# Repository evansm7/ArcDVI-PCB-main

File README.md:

# ArcDVI main board

Kicad 6.0 PCB design for the ArcDVI main board:

This board interfaces via FFC to an ArcDVI VIDC board (either the socket-based interposer for A4xx machines, or the push-on for A3000/A5000).

See <https://stardot.org.uk> for more info.

# License

ArcDVI is copyright 2023 Matt Evans.

This work is licensed under the Creative Commons Attribution-NonCommercial-ShareAlike 3.0 Unported License. To view a copy of this license, visit http://creativecommons.org/licenses/by-nc-sa/3.0/ or send a letter to Creative Commons, PO Box 1866, Mountain View, CA 94042, USA.

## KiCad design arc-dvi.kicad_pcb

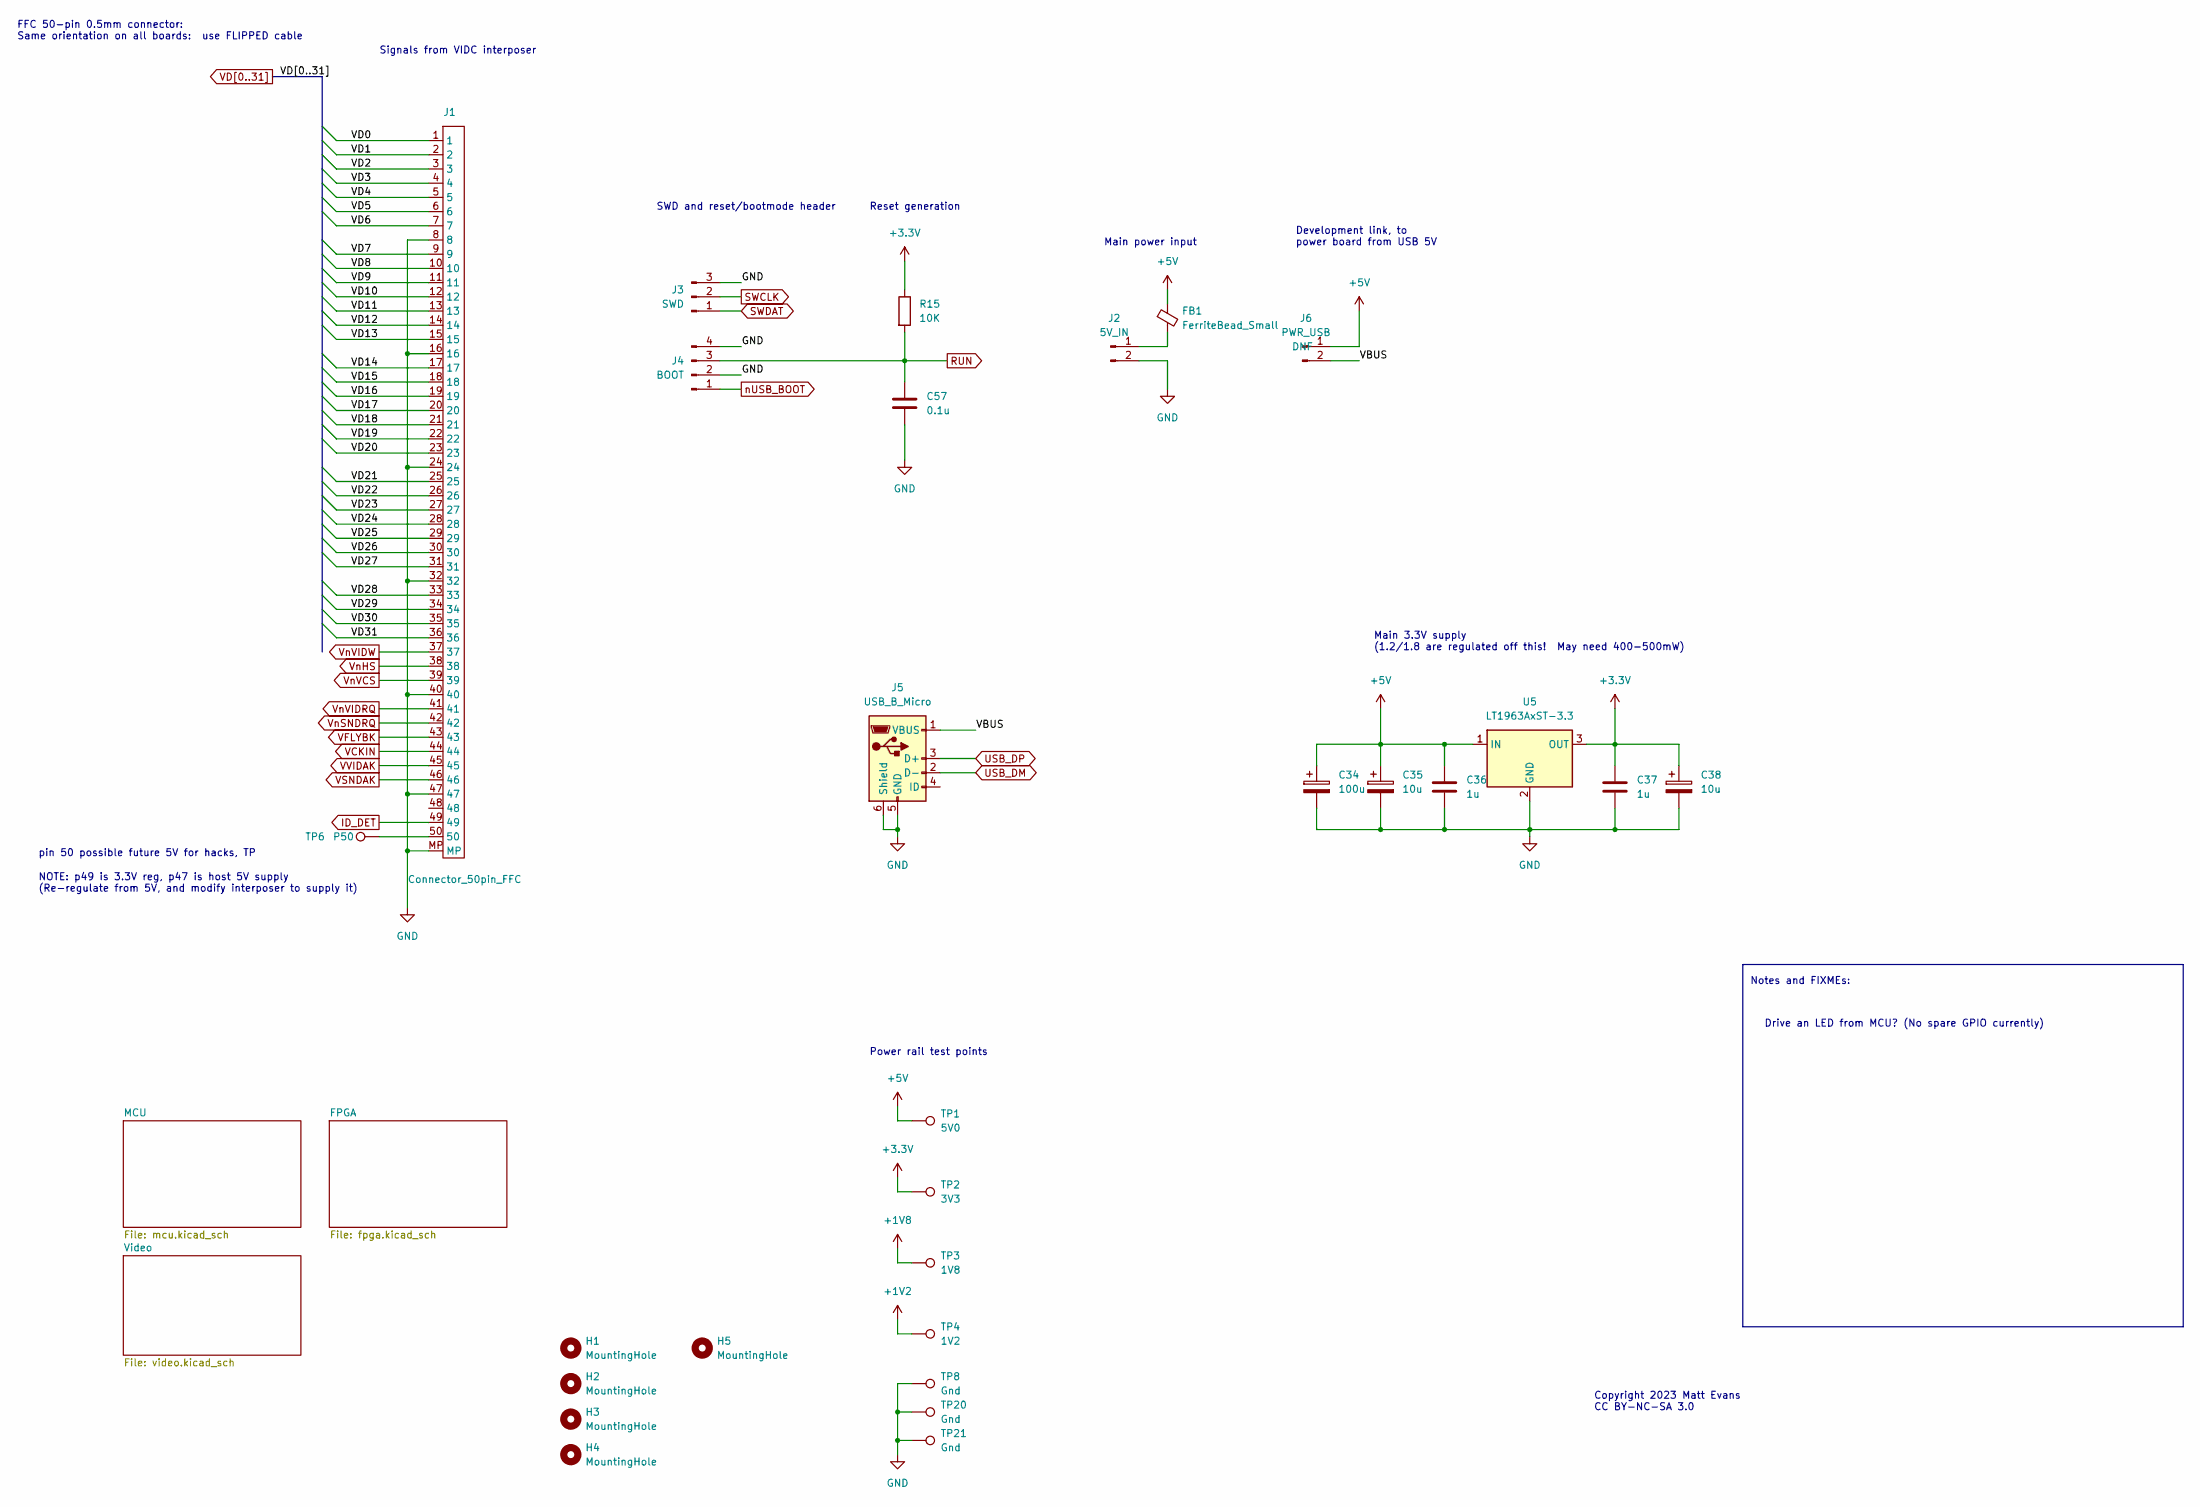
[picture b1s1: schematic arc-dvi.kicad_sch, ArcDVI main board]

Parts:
C34: 100u; CP_EIA-3528-21_Kemet-B
C35, C38: 10u; CP_EIA-3528-21_Kemet-B
C36, C37: 1u; C_0603_1608Metric
C57: 0.1u; C_0603_1608Metric
FB1: FerriteBead_Small; L_0805_2012Metric
H1, H2, H3, H4, H5: MountingHole; MountingHole_3.2mm_M3
J1: Connector_50pin_FFC; Hirose_FH12-50S-0.5SH_1x50-1MP_P0.50mm_Horizontal
J2: 5V_IN; PinHeader_1x02_P2.54mm_Horizontal
J3: SWD; PinHeader_1x03_P2.54mm_Vertical
J4: BOOT; PinHeader_1x04_P2.54mm_Vertical
J5: USB_B_Micro; USB_Micro-B_Amphenol_10104110_Horizontal
J6: PWR_USB; PinHeader_1x02_P2.54mm_Vertical
R15: 10K; R_0603_1608Metric
TP1: 5V0; TestPoint_Pad_1.5x1.5mm
TP2: 3V3; TestPoint_Pad_1.5x1.5mm
TP3: 1V8; TestPoint_Pad_1.5x1.5mm
TP4: 1V2; TestPoint_Pad_1.5x1.5mm
TP6: P50; TestPoint_Pad_D1.0mm
TP8, TP20, TP21: Gnd; TestPoint_Pad_1.5x1.5mm
U5: LT1963AxST-3.3; SOT-223-3_TabPin2

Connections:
+1V2: TP4.1; also elsewhere on the board
+1V8: TP3.1; also elsewhere on the board
+3V3: C37.1, C38.1, R15.1, TP2.1, U5.3 (OUT); also elsewhere on the board
+5V: C34.1, C35.1, C36.1, FB1.1, J6.1, TP1.1, U5.1 (IN); also elsewhere on the board
/VBUS: J5.1 (VBUS), J6.2
GND: C34.2, C35.2, C36.2, C37.2, C38.2, C57.2, J1.8, J1.16, J1.24, J1.32, J1.40, J1.47, J1.MP, J2.2, J3.3, J4.2, J4.4, J5.5 (GND), J5.6 (Shield), TP8.1, TP20.1, TP21.1, U5.2 (GND); also elsewhere on the board
ID_DET: J1.49; also elsewhere on the board
unnamed: FB1.2, J2.1
unnamed: J1.50, TP6.1
RUN: C57.1, J4.3, R15.2; also elsewhere on the board
SWCLK: J3.2; also elsewhere on the board
SWDAT: J3.1; also elsewhere on the board
USB_DM: J5.2 (D-); also elsewhere on the board
USB_DP: J5.3 (D+); also elsewhere on the board
VCKIN: J1.44; also elsewhere on the board
VD0: J1.1; also elsewhere on the board
VD1: J1.2; also elsewhere on the board
VD2: J1.3; also elsewhere on the board
VD3: J1.4; also elsewhere on the board
VD4: J1.5; also elsewhere on the board
VD5: J1.6; also elsewhere on the board
VD6: J1.7; also elsewhere on the board
VD7: J1.9; also elsewhere on the board
VD8: J1.10; also elsewhere on the board
VD9: J1.11; also elsewhere on the board
VD10: J1.12; also elsewhere on the board
VD11: J1.13; also elsewhere on the board
VD12: J1.14; also elsewhere on the board
VD13: J1.15; also elsewhere on the board
VD14: J1.17; also elsewhere on the board
VD15: J1.18; also elsewhere on the board
VD16: J1.19; also elsewhere on the board
VD17: J1.20; also elsewhere on the board
VD18: J1.21; also elsewhere on the board
VD19: J1.22; also elsewhere on the board
VD20: J1.23; also elsewhere on the board
VD21: J1.25; also elsewhere on the board
VD22: J1.26; also elsewhere on the board
VD23: J1.27; also elsewhere on the board
VD24: J1.28; also elsewhere on the board
VD25: J1.29; also elsewhere on the board
VD26: J1.30; also elsewhere on the board
VD27: J1.31; also elsewhere on the board
VD28: J1.33; also elsewhere on the board
VD29: J1.34; also elsewhere on the board
VD30: J1.35; also elsewhere on the board
VD31: J1.36; also elsewhere on the board
VFLYBK: J1.43; also elsewhere on the board
VSNDAK: J1.46; also elsewhere on the board
VVIDAK: J1.45; also elsewhere on the board
VnHS: J1.38; also elsewhere on the board
VnSNDRQ: J1.42; also elsewhere on the board
VnVCS: J1.39; also elsewhere on the board
VnVIDRQ: J1.41; also elsewhere on the board
VnVIDW: J1.37; also elsewhere on the board
nUSB_BOOT: J4.1; also elsewhere on the board

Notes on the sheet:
Reset generation
Notes and FIXMEs:
Power rail test points
Copyright 2023 Matt Evans CC BY-NC-SA 3.0
Development link, to power board from USB 5V
NOTE: p49 is 3.3V reg, p47 is host 5V supply (Re-regulate from 5V, and modify interposer to supply it)
Main 3.3V supply (1.2/1.8 are regulated off this! May need 400-500mW)
Signals from VIDC interposer
SWD and reset/bootmode header
pin 50 possible future 5V for hacks, TP
Drive an LED from MCU? (No spare GPIO currently)
FFC 50-pin 0.5mm connector: Same orientation on all boards: use FLIPPED cable
Main power input

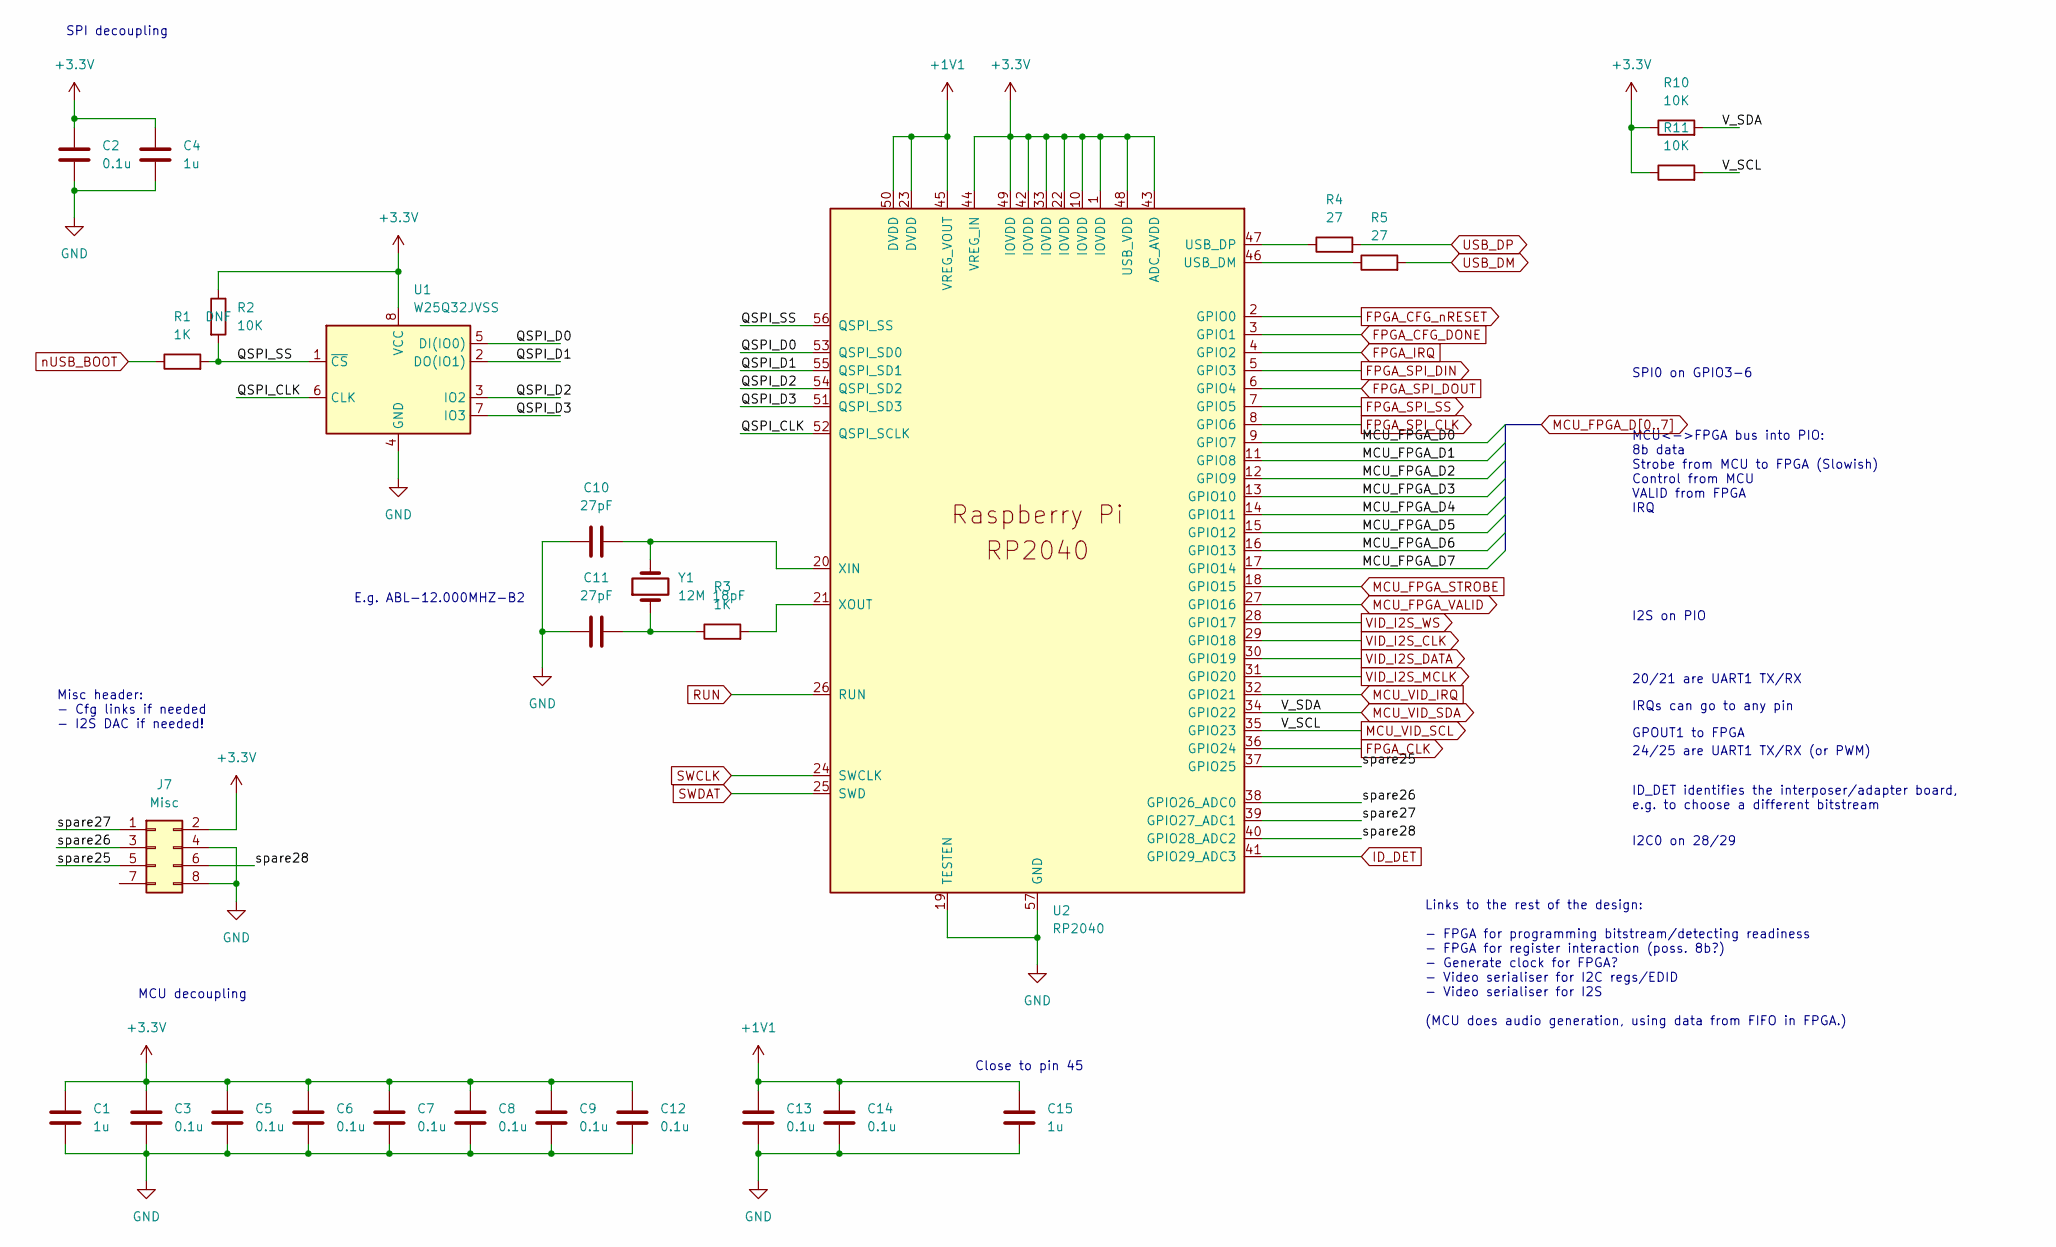
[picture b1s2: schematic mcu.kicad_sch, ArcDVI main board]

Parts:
C1, C4, C15: 1u; C_0603_1608Metric
C2, C3, C5, C6, C7, C8, C9, C12, C13, C14: 0.1u; C_0603_1608Metric
C10, C11: 27pF; C_0603_1608Metric
J7: Misc; PinHeader_2x04_P2.54mm_Vertical
R1, R3: 1K; R_0603_1608Metric
R2, R10, R11: 10K; R_0603_1608Metric
R4, R5: 27; R_0603_1608Metric
U1: W25Q32JVSS; SOIC-8_5.23x5.23mm_P1.27mm
U2: RP2040; RP2040-QFN-56
Y1: 12M 18pF; Crystal_SMD_ABLS7M

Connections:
+1V1: C13.1, C14.1, C15.1, U2.23 (DVDD), U2.45 (VREG_VOUT), U2.50 (DVDD)
+3V3: C1.1, C2.1, C3.1, C4.1, C5.1, C6.1, C7.1, C8.1, C9.1, C12.1, J7.2, R2.1, R10.1, R11.1, U1.8 (VCC), U2.1 (IOVDD), U2.10 (IOVDD), U2.22 (IOVDD), U2.33 (IOVDD), U2.42 (IOVDD), U2.43 (ADC_AVDD), U2.44 (VREG_IN), U2.48 (USB_VDD), U2.49 (IOVDD); also elsewhere on the board
/MCU/QSPI_CLK: U1.6 (CLK), U2.52 (QSPI_SCLK)
/MCU/QSPI_D0: U1.5 (DI(IO0)), U2.53 (QSPI_SD0)
/MCU/QSPI_D1: U1.2 (DO(IO1)), U2.55 (QSPI_SD1)
/MCU/QSPI_D2: U1.3 (IO2), U2.54 (QSPI_SD2)
/MCU/QSPI_D3: U1.7 (IO3), U2.51 (QSPI_SD3)
/MCU/QSPI_SS: R1.2, R2.2, U1.1 (~CS), U2.56 (QSPI_SS)
/MCU/spare25: J7.5, U2.37 (GPIO25)
/MCU/spare26: J7.3, U2.38 (GPIO26_ADC0)
/MCU/spare27: J7.1, U2.39 (GPIO27_ADC1)
/MCU/spare28: J7.6, U2.40 (GPIO28_ADC2)
FPGA_CFG_DONE: U2.3 (GPIO1); also elsewhere on the board
FPGA_CFG_nRESET: U2.2 (GPIO0); also elsewhere on the board
FPGA_CLK: U2.36 (GPIO24); also elsewhere on the board
FPGA_IRQ: U2.4 (GPIO2); also elsewhere on the board
FPGA_SPI_CLK: U2.8 (GPIO6); also elsewhere on the board
FPGA_SPI_DIN: U2.5 (GPIO3); also elsewhere on the board
FPGA_SPI_DOUT: U2.6 (GPIO4); also elsewhere on the board
FPGA_SPI_SS: U2.7 (GPIO5); also elsewhere on the board
GND: C1.2, C2.2, C3.2, C4.2, C5.2, C6.2, C7.2, C8.2, C9.2, C10.1, C11.1, C12.2, C13.2, C14.2, C15.2, J7.4, J7.8, U1.4 (GND), U2.19 (TESTEN), U2.57 (GND); also elsewhere on the board
ID_DET: U2.41 (GPIO29_ADC3); also elsewhere on the board
MCU_FPGA_D0: U2.9 (GPIO7); also elsewhere on the board
MCU_FPGA_D1: U2.11 (GPIO8); also elsewhere on the board
MCU_FPGA_D2: U2.12 (GPIO9); also elsewhere on the board
MCU_FPGA_D3: U2.13 (GPIO10); also elsewhere on the board
MCU_FPGA_D4: U2.14 (GPIO11); also elsewhere on the board
MCU_FPGA_D5: U2.15 (GPIO12); also elsewhere on the board
MCU_FPGA_D6: U2.16 (GPIO13); also elsewhere on the board
MCU_FPGA_D7: U2.17 (GPIO14); also elsewhere on the board
MCU_FPGA_STROBE: U2.18 (GPIO15); also elsewhere on the board
MCU_FPGA_VALID: U2.27 (GPIO16); also elsewhere on the board
MCU_VID_IRQ: U2.32 (GPIO21); also elsewhere on the board
MCU_VID_SCL: R11.2, U2.35 (GPIO23); also elsewhere on the board
MCU_VID_SDA: R10.2, U2.34 (GPIO22); also elsewhere on the board
unnamed: C10.2, U2.20 (XIN), Y1.2
unnamed: C11.2, R3.1, Y1.1
unnamed: R3.2, U2.21 (XOUT)
unnamed: R4.1, U2.47 (USB_DP)
unnamed: R5.1, U2.46 (USB_DM)
RUN: U2.26 (RUN); also elsewhere on the board
SWCLK: U2.24 (SWCLK); also elsewhere on the board
SWDAT: U2.25 (SWD); also elsewhere on the board
USB_DM: R5.2; also elsewhere on the board
USB_DP: R4.2; also elsewhere on the board
VID_I2S_CLK: U2.29 (GPIO18); also elsewhere on the board
VID_I2S_DATA: U2.30 (GPIO19); also elsewhere on the board
VID_I2S_MCLK: U2.31 (GPIO20); also elsewhere on the board
VID_I2S_WS: U2.28 (GPIO17); also elsewhere on the board
nUSB_BOOT: R1.1; also elsewhere on the board

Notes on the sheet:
MCU decoupling
20/21 are UART1 TX/RX
Misc header: - Cfg links if needed - I2S DAC if needed!
Links to the rest of the design: - FPGA for programming bitstream/detecting readiness - FPGA for register interaction (poss. 8b?) - Generate clock for FPGA? - Video serialiser for I2C regs/EDID - Video serialiser for I2S (MCU does audio generation, using data from FIFO in FPGA.)
IRQs can go to any pin
E.g. ABL-12.000MHZ-B2
I2S on PIO
GPOUT1 to FPGA
SPI decoupling
24/25 are UART1 TX/RX (or PWM)
I2C0 on 28/29
Close to pin 45
MCU<->FPGA bus into PIO: 8b data Strobe from MCU to FPGA (Slowish) Control from MCU VALID from FPGA IRQ
SPI0 on GPIO3-6
ID_DET identifies the interposer/adapter board, e.g. to choose a different bitstream

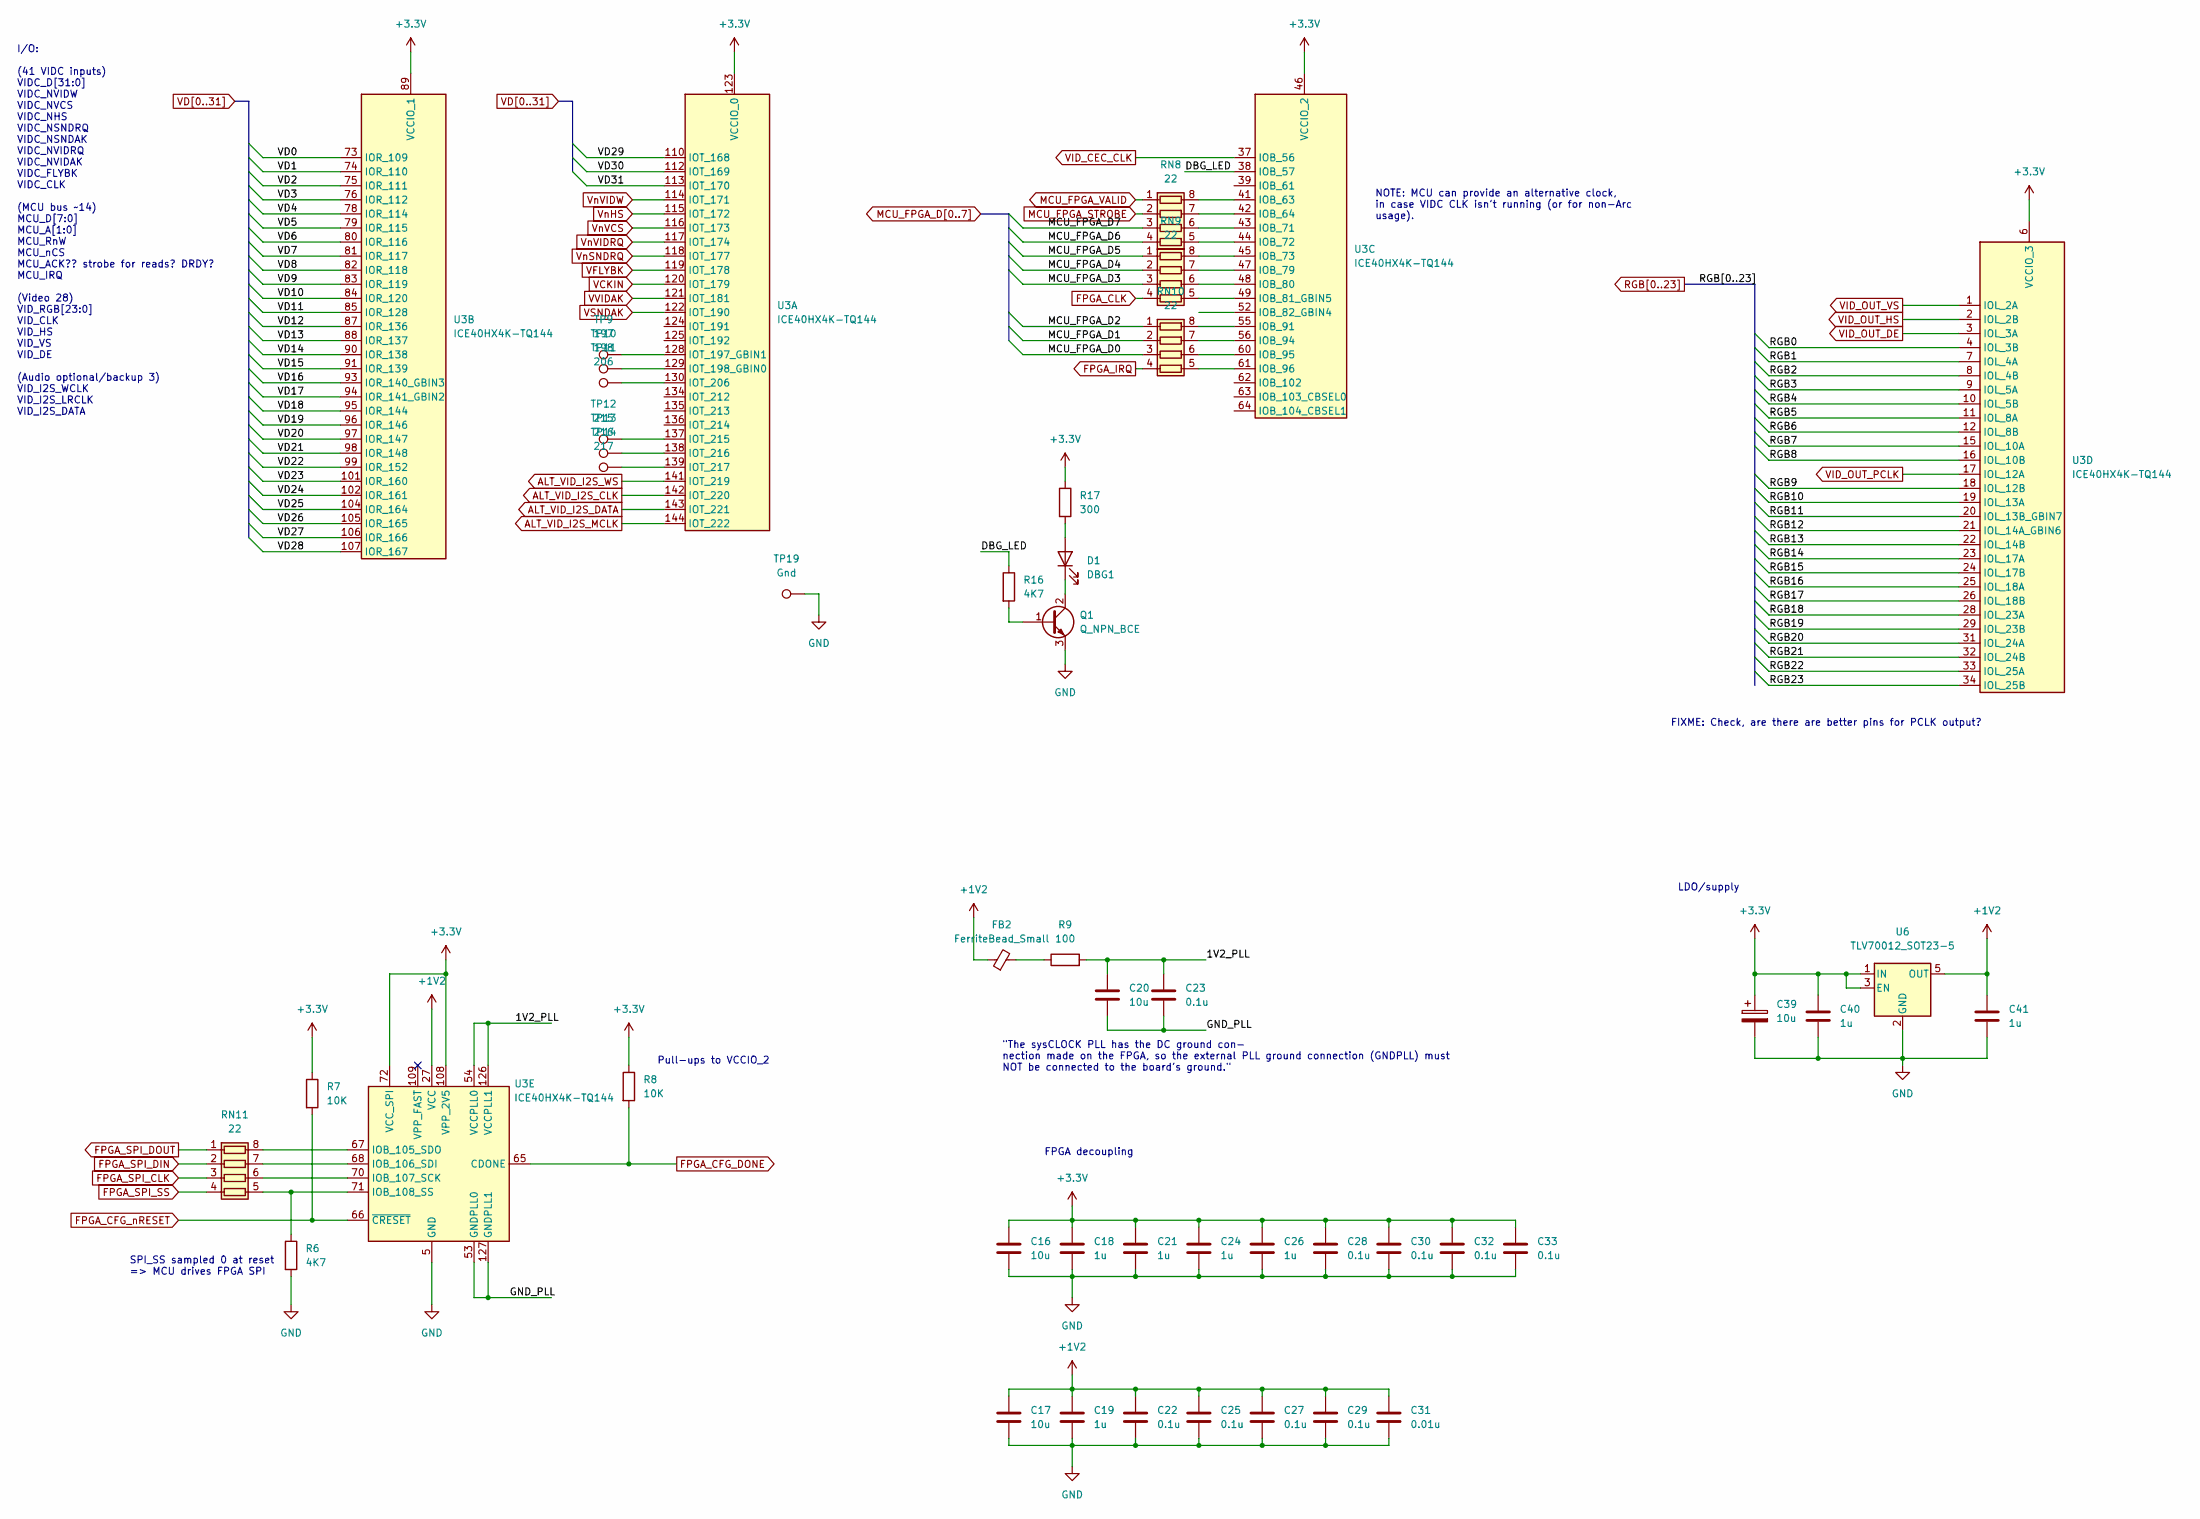
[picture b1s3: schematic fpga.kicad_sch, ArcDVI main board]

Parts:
C16, C17, C20: 10u; C_0805_2012Metric
C18, C19, C21, C24, C26, C40, C41: 1u; C_0603_1608Metric
C22, C23, C25, C27, C28, C29, C30, C32, C33: 0.1u; C_0603_1608Metric
C31: 0.01u; C_0603_1608Metric
C39: 10u; CP_EIA-3528-21_Kemet-B
D1: DBG1; LED_0805_2012Metric
FB2: FerriteBead_Small; L_0603_1608Metric
Q1: Q_NPN_BCE; SOT-23
R6, R16: 4K7; R_0603_1608Metric
R7, R8: 10K; R_0603_1608Metric
R9: 100; R_0603_1608Metric
R17: 300; R_0603_1608Metric
RN8, RN9, RN10, RN11: 22; R_Array_Convex_4x0603
TP9: 197; TestPoint_Pad_D1.0mm
TP10: 198; TestPoint_Pad_D1.0mm
TP11: 206; TestPoint_Pad_D1.0mm
TP12: 215; TestPoint_Pad_D1.0mm
TP13: 216; TestPoint_Pad_D1.0mm
TP14: 217; TestPoint_Pad_D1.0mm
TP19: Gnd; TestPoint_Pad_1.5x1.5mm
U3: ICE40HX4K-TQ144; TQFP-144_20x20mm_P0.5mm
U6: TLV70012_SOT23-5; SOT-23-5

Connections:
+1V2: C17.1, C19.1, C22.1, C25.1, C27.1, C29.1, C31.1, C41.1, FB2.1, U3.27 (VCC), U3.40 (VCC), U3.92 (VCC), U3.111 (VCC), U6.5 (OUT); also elsewhere on the board
+3V3: C16.1, C18.1, C21.1, C24.1, C26.1, C28.1, C30.1, C32.1, C33.1, C39.1, C40.1, R7.1, R8.1, R17.1, U3.6 (VCCIO_3), U3.30 (VCCIO_3), U3.46 (VCCIO_2), U3.57 (VCCIO_2), U3.72 (VCC_SPI), U3.89 (VCCIO_1), U3.100 (VCCIO_1), U3.108 (VPP_2V5), U3.123 (VCCIO_0), U3.131 (VCCIO_0), U6.1 (IN), U6.3 (EN); also elsewhere on the board
/FPGA/1V2_PLL: C20.1, C23.1, R9.2, U3.54 (VCCPLL0), U3.126 (VCCPLL1)
/FPGA/DBG_LED: R16.1, U3.38 (IOB_57)
/FPGA/GND_PLL: C20.2, C23.2, U3.53 (GNDPLL0), U3.127 (GNDPLL1)
ALT_VID_I2S_CLK: U3.142 (IOT_220); also elsewhere on the board
ALT_VID_I2S_DATA: U3.143 (IOT_221); also elsewhere on the board
ALT_VID_I2S_MCLK: U3.144 (IOT_222); also elsewhere on the board
ALT_VID_I2S_WS: U3.141 (IOT_219); also elsewhere on the board
FPGA_CFG_DONE: R8.2, U3.65 (CDONE); also elsewhere on the board
FPGA_CFG_nRESET: R7.2, U3.66 (~CRESET); also elsewhere on the board
FPGA_CLK: RN9.4 (R4.1); also elsewhere on the board
FPGA_IRQ: RN10.4 (R4.1); also elsewhere on the board
FPGA_SPI_CLK: RN11.3 (R3.1); also elsewhere on the board
FPGA_SPI_DIN: RN11.2 (R2.1); also elsewhere on the board
FPGA_SPI_DOUT: RN11.1 (R1.1); also elsewhere on the board
FPGA_SPI_SS: RN11.4 (R4.1); also elsewhere on the board
GND: C16.2, C17.2, C18.2, C19.2, C21.2, C22.2, C24.2, C25.2, C26.2, C27.2, C28.2, C29.2, C30.2, C31.2, C32.2, C33.2, C39.2, C40.2, C41.2, Q1.3 (E), R6.2, TP19.1, U3.5 (GND), U3.13 (GND), U3.14 (GND), U3.59 (GND), U3.69 (GND), U3.86 (GND), U3.103 (GND), U3.132 (GND), U3.140 (GND), U6.2 (GND); also elsewhere on the board
MCU_FPGA_D0: RN10.3 (R3.1); also elsewhere on the board
MCU_FPGA_D1: RN10.2 (R2.1); also elsewhere on the board
MCU_FPGA_D2: RN10.1 (R1.1); also elsewhere on the board
MCU_FPGA_D3: RN9.3 (R3.1); also elsewhere on the board
MCU_FPGA_D4: RN9.2 (R2.1); also elsewhere on the board
MCU_FPGA_D5: RN9.1 (R1.1); also elsewhere on the board
MCU_FPGA_D6: RN8.4 (R4.1); also elsewhere on the board
MCU_FPGA_D7: RN8.3 (R3.1); also elsewhere on the board
MCU_FPGA_STROBE: RN8.2 (R2.1); also elsewhere on the board
MCU_FPGA_VALID: RN8.1 (R1.1); also elsewhere on the board
unnamed: D1.1 (K), Q1.2 (C)
unnamed: D1.2 (A), R17.2
unnamed: FB2.2, R9.1
unnamed: Q1.1 (B), R16.2
unnamed: R6.1, RN11.5 (R4.2), U3.71 (IOB_108_SS)
unnamed: RN8.5 (R4.2), U3.44 (IOB_72)
unnamed: RN8.6 (R3.2), U3.43 (IOB_71)
unnamed: RN8.7 (R2.2), U3.42 (IOB_64)
unnamed: RN8.8 (R1.2), U3.41 (IOB_63)
unnamed: RN9.5 (R4.2), U3.49 (IOB_81_GBIN5)
unnamed: RN9.6 (R3.2), U3.48 (IOB_80)
unnamed: RN9.7 (R2.2), U3.47 (IOB_79)
unnamed: RN9.8 (R1.2), U3.45 (IOB_73)
unnamed: RN10.5 (R4.2), U3.61 (IOB_96)
unnamed: RN10.6 (R3.2), U3.60 (IOB_95)
unnamed: RN10.7 (R2.2), U3.56 (IOB_94)
unnamed: RN10.8 (R1.2), U3.55 (IOB_91)
unnamed: RN11.6 (R3.2), U3.70 (IOB_107_SCK)
unnamed: RN11.7 (R2.2), U3.68 (IOB_106_SDI)
unnamed: RN11.8 (R1.2), U3.67 (IOB_105_SDO)
unnamed: TP9.1, U3.128 (IOT_197_GBIN1)
unnamed: TP10.1, U3.129 (IOT_198_GBIN0)
unnamed: TP11.1, U3.130 (IOT_206)
unnamed: TP12.1, U3.137 (IOT_215)
unnamed: TP13.1, U3.138 (IOT_216)
unnamed: TP14.1, U3.139 (IOT_217)
RGB0: U3.4 (IOL_3B); also elsewhere on the board
RGB1: U3.7 (IOL_4A); also elsewhere on the board
RGB2: U3.8 (IOL_4B); also elsewhere on the board
RGB3: U3.9 (IOL_5A); also elsewhere on the board
RGB4: U3.10 (IOL_5B); also elsewhere on the board
RGB5: U3.11 (IOL_8A); also elsewhere on the board
RGB6: U3.12 (IOL_8B); also elsewhere on the board
RGB7: U3.15 (IOL_10A); also elsewhere on the board
RGB8: U3.16 (IOL_10B); also elsewhere on the board
RGB9: U3.18 (IOL_12B); also elsewhere on the board
RGB10: U3.19 (IOL_13A); also elsewhere on the board
RGB11: U3.20 (IOL_13B_GBIN7); also elsewhere on the board
RGB12: U3.21 (IOL_14A_GBIN6); also elsewhere on the board
RGB13: U3.22 (IOL_14B); also elsewhere on the board
RGB14: U3.23 (IOL_17A); also elsewhere on the board
RGB15: U3.24 (IOL_17B); also elsewhere on the board
RGB16: U3.25 (IOL_18A); also elsewhere on the board
RGB17: U3.26 (IOL_18B); also elsewhere on the board
RGB18: U3.28 (IOL_23A); also elsewhere on the board
RGB19: U3.29 (IOL_23B); also elsewhere on the board
RGB20: U3.31 (IOL_24A); also elsewhere on the board
RGB21: U3.32 (IOL_24B); also elsewhere on the board
RGB22: U3.33 (IOL_25A); also elsewhere on the board
RGB23: U3.34 (IOL_25B); also elsewhere on the board
VCKIN: U3.120 (IOT_179); also elsewhere on the board
VD0: U3.73 (IOR_109); also elsewhere on the board
VD1: U3.74 (IOR_110); also elsewhere on the board
VD2: U3.75 (IOR_111); also elsewhere on the board
VD3: U3.76 (IOR_112); also elsewhere on the board
VD4: U3.78 (IOR_114); also elsewhere on the board
VD5: U3.79 (IOR_115); also elsewhere on the board
VD6: U3.80 (IOR_116); also elsewhere on the board
VD7: U3.81 (IOR_117); also elsewhere on the board
VD8: U3.82 (IOR_118); also elsewhere on the board
VD9: U3.83 (IOR_119); also elsewhere on the board
VD10: U3.84 (IOR_120); also elsewhere on the board
VD11: U3.85 (IOR_128); also elsewhere on the board
VD12: U3.87 (IOR_136); also elsewhere on the board
VD13: U3.88 (IOR_137); also elsewhere on the board
VD14: U3.90 (IOR_138); also elsewhere on the board
VD15: U3.91 (IOR_139); also elsewhere on the board
VD16: U3.93 (IOR_140_GBIN3); also elsewhere on the board
VD17: U3.94 (IOR_141_GBIN2); also elsewhere on the board
VD18: U3.95 (IOR_144); also elsewhere on the board
VD19: U3.96 (IOR_146); also elsewhere on the board
VD20: U3.97 (IOR_147); also elsewhere on the board
VD21: U3.98 (IOR_148); also elsewhere on the board
VD22: U3.99 (IOR_152); also elsewhere on the board
VD23: U3.101 (IOR_160); also elsewhere on the board
VD24: U3.102 (IOR_161); also elsewhere on the board
VD25: U3.104 (IOR_164); also elsewhere on the board
VD26: U3.105 (IOR_165); also elsewhere on the board
VD27: U3.106 (IOR_166); also elsewhere on the board
VD28: U3.107 (IOR_167); also elsewhere on the board
VD29: U3.110 (IOT_168); also elsewhere on the board
VD30: U3.112 (IOT_169); also elsewhere on the board
VD31: U3.113 (IOT_170); also elsewhere on the board
VFLYBK: U3.119 (IOT_178); also elsewhere on the board
VID_CEC_CLK: U3.37 (IOB_56); also elsewhere on the board
VID_OUT_DE: U3.3 (IOL_3A); also elsewhere on the board
VID_OUT_HS: U3.2 (IOL_2B); also elsewhere on the board
VID_OUT_PCLK: U3.17 (IOL_12A); also elsewhere on the board
VID_OUT_VS: U3.1 (IOL_2A); also elsewhere on the board
VSNDAK: U3.122 (IOT_190); also elsewhere on the board
VVIDAK: U3.121 (IOT_181); also elsewhere on the board
VnHS: U3.115 (IOT_172); also elsewhere on the board
VnSNDRQ: U3.118 (IOT_177); also elsewhere on the board
VnVCS: U3.116 (IOT_173); also elsewhere on the board
VnVIDRQ: U3.117 (IOT_174); also elsewhere on the board
VnVIDW: U3.114 (IOT_171); also elsewhere on the board

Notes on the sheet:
Pull-ups to VCCIO_2
SPI_SS sampled 0 at reset => MCU drives FPGA SPI
FIXME: Check, are there are better pins for PCLK output?
LDO/supply
"The sysCLOCK PLL has the DC ground con- nection made on the FPGA, so the external PLL ground connection (GNDPLL) must NOT be connected to the board's ground."
FPGA decoupling
I/O: (41 VIDC inputs) VIDC_D[31:0] VIDC_NVIDW VIDC_NVCS VIDC_NHS VIDC_NSNDRQ VIDC_NSNDAK VIDC_NVIDRQ VIDC_NVIDAK VIDC_FLYBK VIDC_CLK (MCU bus ~14) MCU_D[7:0] MCU_A[1:0] MCU_RnW MCU_nCS MCU_ACK?? strobe for reads? DRDY? MCU_IRQ (Video 28) VID_RGB[23:0] VID_CLK VID_HS VID_VS VID_DE (Audio optional/ba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
NOTE: MCU can provide an alternative clock, in case VIDC CLK isn't running (or for non-Arc usage).

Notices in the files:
arc-dvi.kicad_pcb:
(c) 2023
